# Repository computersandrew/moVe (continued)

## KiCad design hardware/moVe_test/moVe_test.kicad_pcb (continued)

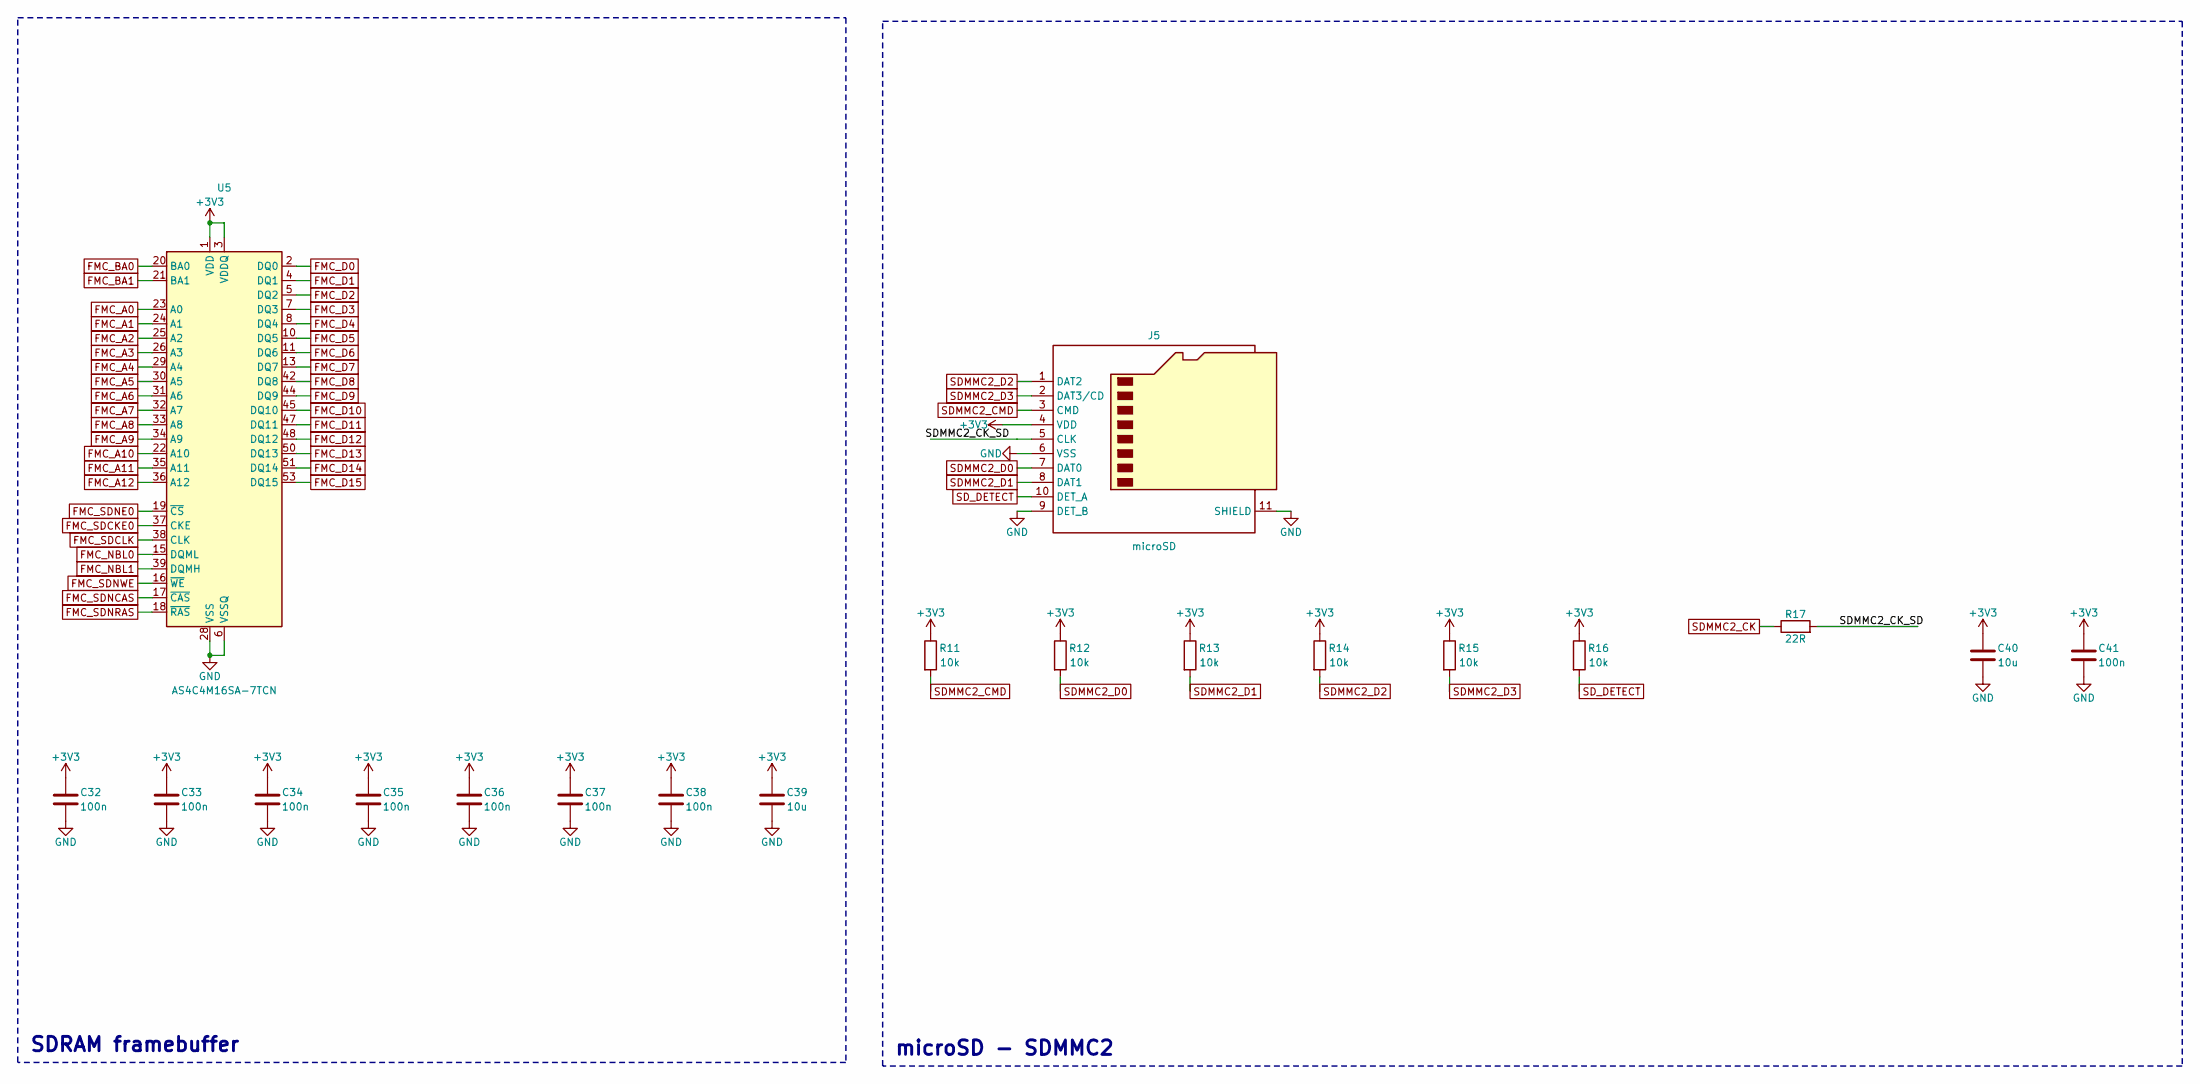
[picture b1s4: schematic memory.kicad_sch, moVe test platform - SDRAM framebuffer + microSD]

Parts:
C32, C33, C34, C35, C36, C37, C38, C41: 100n; C_0603_1608Metric
C39, C40: 10u; C_0805_2012Metric
J5: microSD; microSD_HC_Molex_104031-0811; MPN 1040310811
R11, R12, R13, R14, R15, R16: 10k; R_0603_1608Metric
R17: 22R; R_0603_1608Metric
U5: AS4C4M16SA-7TCN; TSOP-II-54_22.2x10.16mm_P0.8mm; MPN AS4C4M16SA-7TCN (alt MT48LC16M16A2P-6A: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

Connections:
+3V3: C32.1, C33.1, C34.1, C35.1, C36.1, C37.1, C38.1, C39.1, C40.1, C41.1, J5.4 (VDD), R11.1, R12.1, R13.1, R14.1, R15.1, R16.1, U5.1 (VDD), U5.3 (VDDQ), U5.9 (VDDQ), U5.14 (VDD), U5.27 (VDD), U5.43 (VDDQ), U5.49 (VDDQ); also elsewhere on the board
/Memory/SDMMC2_CK_SD: J5.5 (CLK), R17.2
FMC_A0: U5.23 (A0); also elsewhere on the board
FMC_A1: U5.24 (A1); also elsewhere on the board
FMC_A2: U5.25 (A2); also elsewhere on the board
FMC_A3: U5.26 (A3); also elsewhere on the board
FMC_A4: U5.29 (A4); also elsewhere on the board
FMC_A5: U5.30 (A5); also elsewhere on the board
FMC_A6: U5.31 (A6); also elsewhere on the board
FMC_A7: U5.32 (A7); also elsewhere on the board
FMC_A8: U5.33 (A8); also elsewhere on the board
FMC_A9: U5.34 (A9); also elsewhere on the board
FMC_A10: U5.22 (A10); also elsewhere on the board
FMC_A11: U5.35 (A11); also elsewhere on the board
FMC_A12: U5.36 (A12); also elsewhere on the board
FMC_BA0: U5.20 (BA0); also elsewhere on the board
FMC_BA1: U5.21 (BA1); also elsewhere on the board
FMC_D0: U5.2 (DQ0); also elsewhere on the board
FMC_D1: U5.4 (DQ1); also elsewhere on the board
FMC_D2: U5.5 (DQ2); also elsewhere on the board
FMC_D3: U5.7 (DQ3); also elsewhere on the board
FMC_D4: U5.8 (DQ4); also elsewhere on the board
FMC_D5: U5.10 (DQ5); also elsewhere on the board
FMC_D6: U5.11 (DQ6); also elsewhere on the board
FMC_D7: U5.13 (DQ7); also elsewhere on the board
FMC_D8: U5.42 (DQ8); also elsewhere on the board
FMC_D9: U5.44 (DQ9); also elsewhere on the board
FMC_D10: U5.45 (DQ10); also elsewhere on the board
FMC_D11: U5.47 (DQ11); also elsewhere on the board
FMC_D12: U5.48 (DQ12); also elsewhere on the board
FMC_D13: U5.50 (DQ13); also elsewhere on the board
FMC_D14: U5.51 (DQ14); also elsewhere on the board
FMC_D15: U5.53 (DQ15); also elsewhere on the board
FMC_NBL0: U5.15 (DQML); also elsewhere on the board
FMC_NBL1: U5.39 (DQMH); also elsewhere on the board
FMC_SDCKE0: U5.37 (CKE); also elsewhere on the board
FMC_SDCLK: U5.38 (CLK); also elsewhere on the board
FMC_SDNCAS: U5.17 (~CAS); also elsewhere on the board
FMC_SDNE0: U5.19 (~CS); also elsewhere on the board
FMC_SDNRAS: U5.18 (~RAS); also elsewhere on the board
FMC_SDNWE: U5.16 (~WE); also elsewhere on the board
GND: C32.2, C33.2, C34.2, C35.2, C36.2, C37.2, C38.2, C39.2, C40.2, C41.2, J5.6 (VSS), J5.9 (DET_B), J5.11 (SHIELD), U5.6 (VSSQ), U5.12 (VSSQ), U5.28 (VSS), U5.41 (VSS), U5.46 (VSSQ), U5.52 (VSSQ), U5.54 (VSS); also elsewhere on the board
SDMMC2_CK: R17.1; also elsewhere on the board
SDMMC2_CMD: J5.3 (CMD), R11.2; also elsewhere on the board
SDMMC2_D0: J5.7 (DAT0), R12.2; also elsewhere on the board
SDMMC2_D1: J5.8 (DAT1), R13.2; also elsewhere on the board
SDMMC2_D2: J5.1 (DAT2), R14.2; also elsewhere on the board
SDMMC2_D3: J5.2 (DAT3/CD), R15.2; also elsewhere on the board
SD_DETECT: J5.10 (DET_A), R16.2; also elsewhere on the board

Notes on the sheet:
SDRAM framebuffer
microSD - SDMMC2

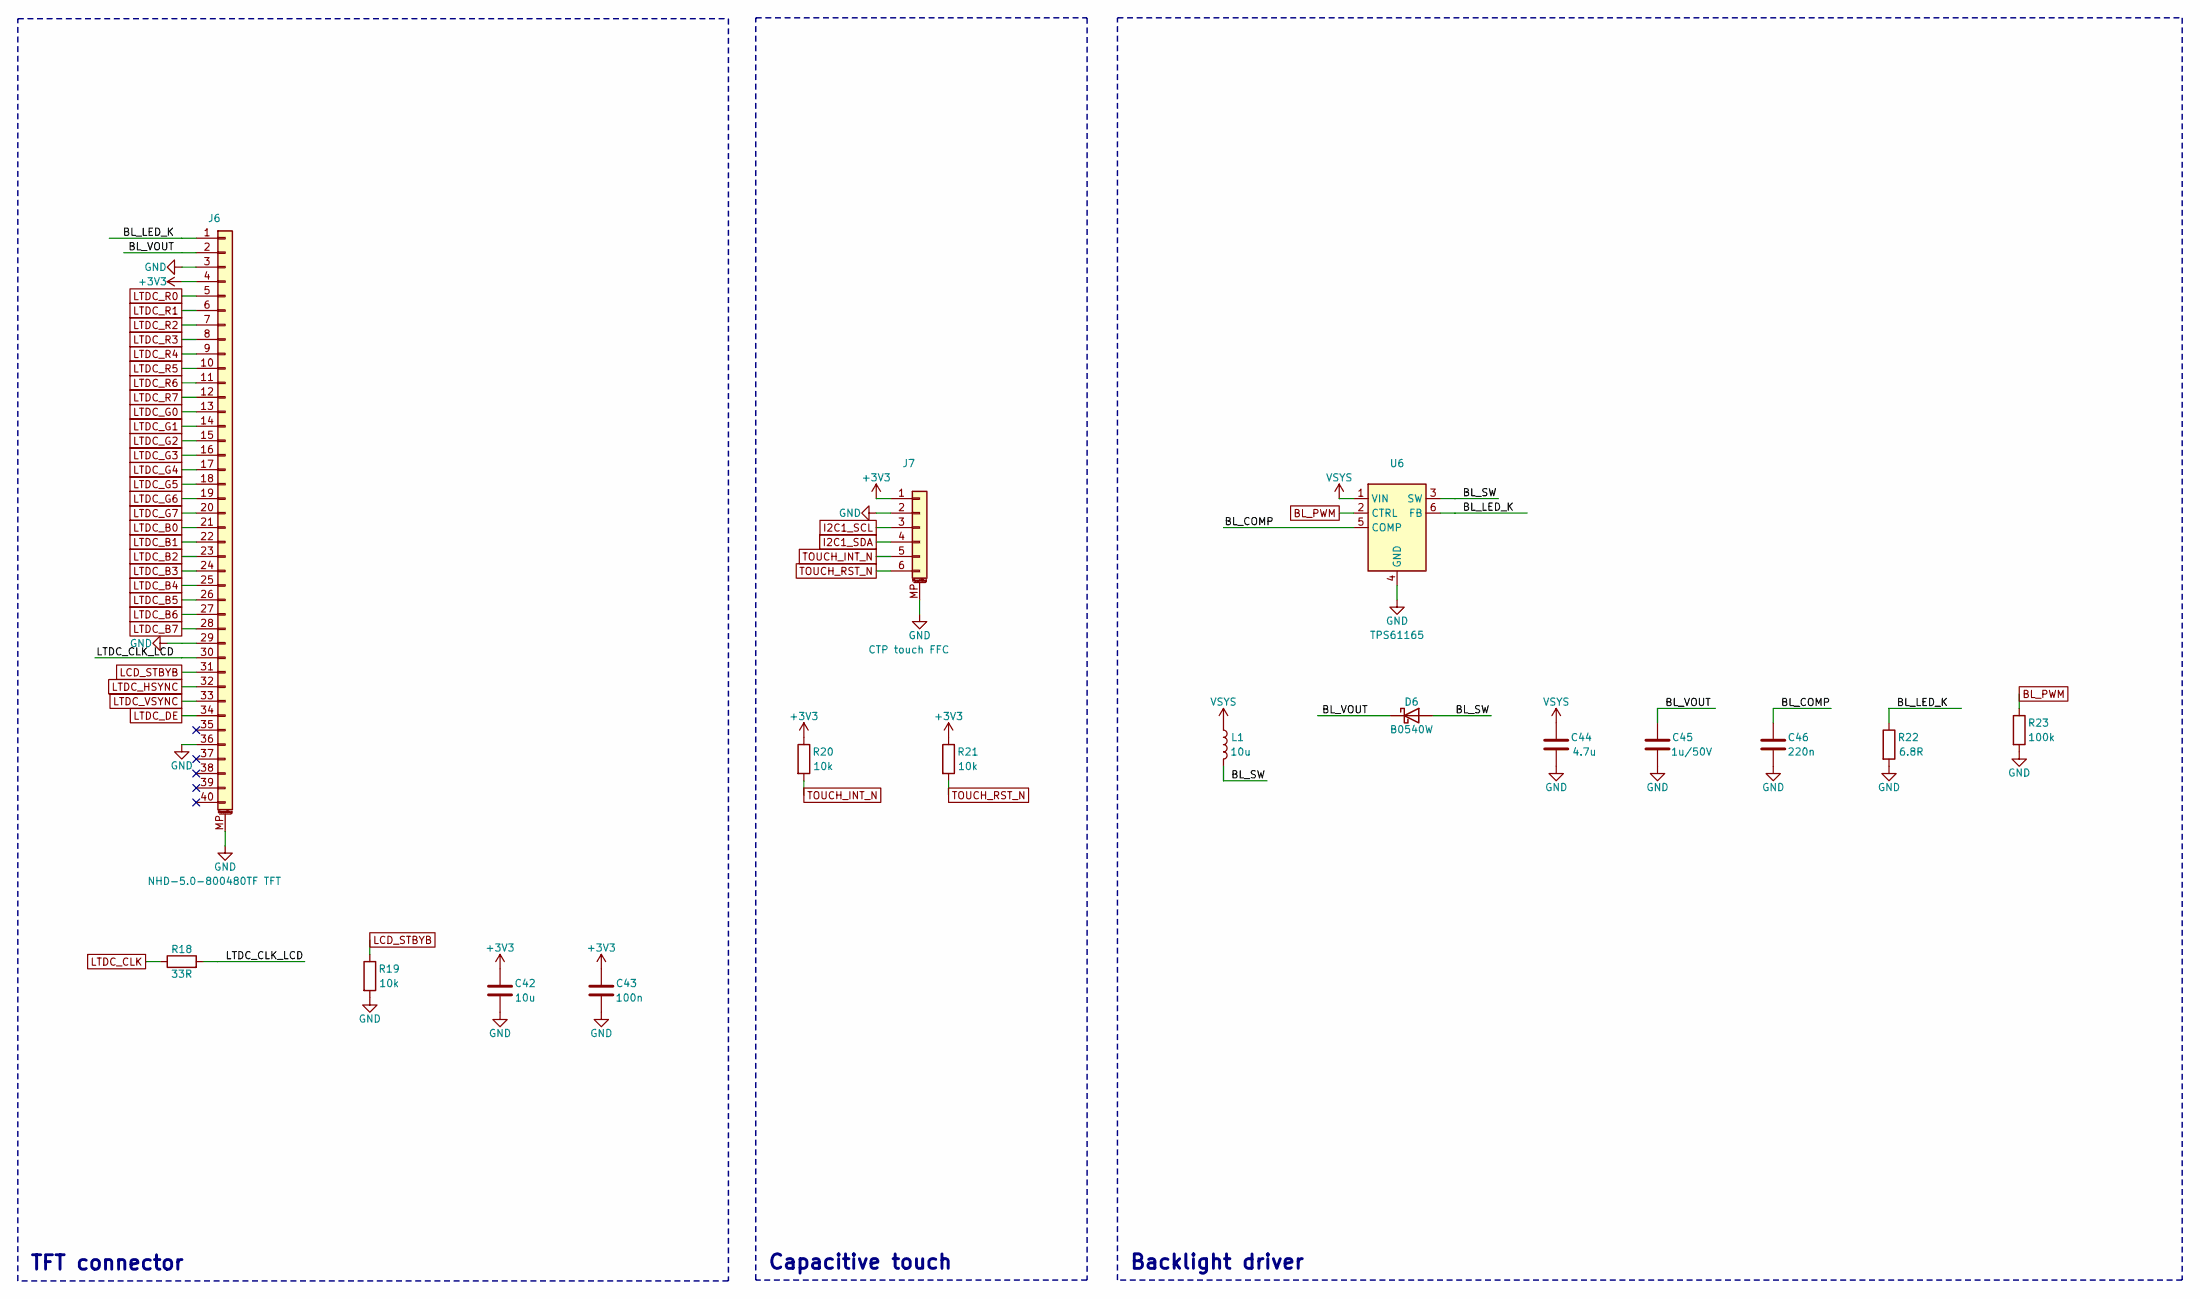
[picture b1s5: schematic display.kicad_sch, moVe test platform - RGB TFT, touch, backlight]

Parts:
C42: 10u; C_0805_2012Metric
C43: 100n; C_0603_1608Metric
C44: 4.7u; C_0805_2012Metric
C45: 1u/50V; C_0805_2012Metric
C46: 220n; C_0603_1608Metric
D6: B0540W; D_SOD-123; MPN B0540W-7-F
J6: NHD-5.0-800480TF TFT; Hirose_FH12-40S-0.5SH_1x40-1MP_P0.50mm_Horizontal; MPN FH12-40S-0.5SH(55) (display spec lists 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
J7: CTP touch FFC; Molex_200528-0060_1x06-1MP_P1.00mm_Horizontal; MPN Molex 200528-0060 (display spec lists 5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
L1: 10u; L_Bourns-SRN4018; MPN SRN4018-100M
R18: 33R; R_0603_1608Metric
R19, R20, R21: 10k; R_0603_1608Metric
R22: 6.8R; R_0603_1608Metric
R23: 100k; R_0603_1608Metric
U6: TPS61165; SOT-23-6; MPN TPS61165DBVR

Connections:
+3V3: C42.1, C43.1, J6.4, J7.1, R20.1, R21.1; also elsewhere on the board
/Display/BL_COMP: C46.1, U6.5 (COMP)
/Display/BL_LED_K: J6.1, R22.1, U6.6 (FB)
/Display/BL_SW: D6.2 (A), L1.2, U6.3 (SW)
/Display/BL_VOUT: C45.1, D6.1 (K), J6.2
/Display/LTDC_CLK_LCD: J6.30, R18.2
BL_PWM: R23.1, U6.2 (CTRL); also elsewhere on the board
GND: C42.2, C43.2, C44.2, C45.2, C46.2, J6.3, J6.29, J6.36, J6.MP (MountPin), J7.2, J7.MP (MountPin), R19.2, R22.2, R23.2, U6.4 (GND); also elsewhere on the board
I2C1_SCL: J7.3; also elsewhere on the board
I2C1_SDA: J7.4; also elsewhere on the board
LCD_STBYB: J6.31, R19.1; also elsewhere on the board
LTDC_B0: J6.21; also elsewhere on the board
LTDC_B1: J6.22; also elsewhere on the board
LTDC_B2: J6.23; also elsewhere on the board
LTDC_B3: J6.24; also elsewhere on the board
LTDC_B4: J6.25; also elsewhere on the board
LTDC_B5: J6.26; also elsewhere on the board
LTDC_B6: J6.27; also elsewhere on the board
LTDC_B7: J6.28; also elsewhere on the board
LTDC_CLK: R18.1; also elsewhere on the board
LTDC_DE: J6.34; also elsewhere on the board
LTDC_G0: J6.13; also elsewhere on the board
LTDC_G1: J6.14; also elsewhere on the board
LTDC_G2: J6.15; also elsewhere on the board
LTDC_G3: J6.16; also elsewhere on the board
LTDC_G4: J6.17; also elsewhere on the board
LTDC_G5: J6.18; also elsewhere on the board
LTDC_G6: J6.19; also elsewhere on the board
LTDC_G7: J6.20; also elsewhere on the board
LTDC_HSYNC: J6.32; also elsewhere on the board
LTDC_R0: J6.5; also elsewhere on the board
LTDC_R1: J6.6; also elsewhere on the board
LTDC_R2: J6.7; also elsewhere on the board
LTDC_R3: J6.8; also elsewhere on the board
LTDC_R4: J6.9; also elsewhere on the board
LTDC_R5: J6.10; also elsewhere on the board
LTDC_R6: J6.11; also elsewhere on the board
LTDC_R7: J6.12; also elsewhere on the board
LTDC_VSYNC: J6.33; also elsewhere on the board
TOUCH_INT_N: J7.5, R20.2; also elsewhere on the board
TOUCH_RST_N: J7.6, R21.2; also elsewhere on the board
VSYS: C44.1, L1.1, U6.1 (VIN); also elsewhere on the board

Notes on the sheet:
TFT connector
Capacitive touch
Backlight driver

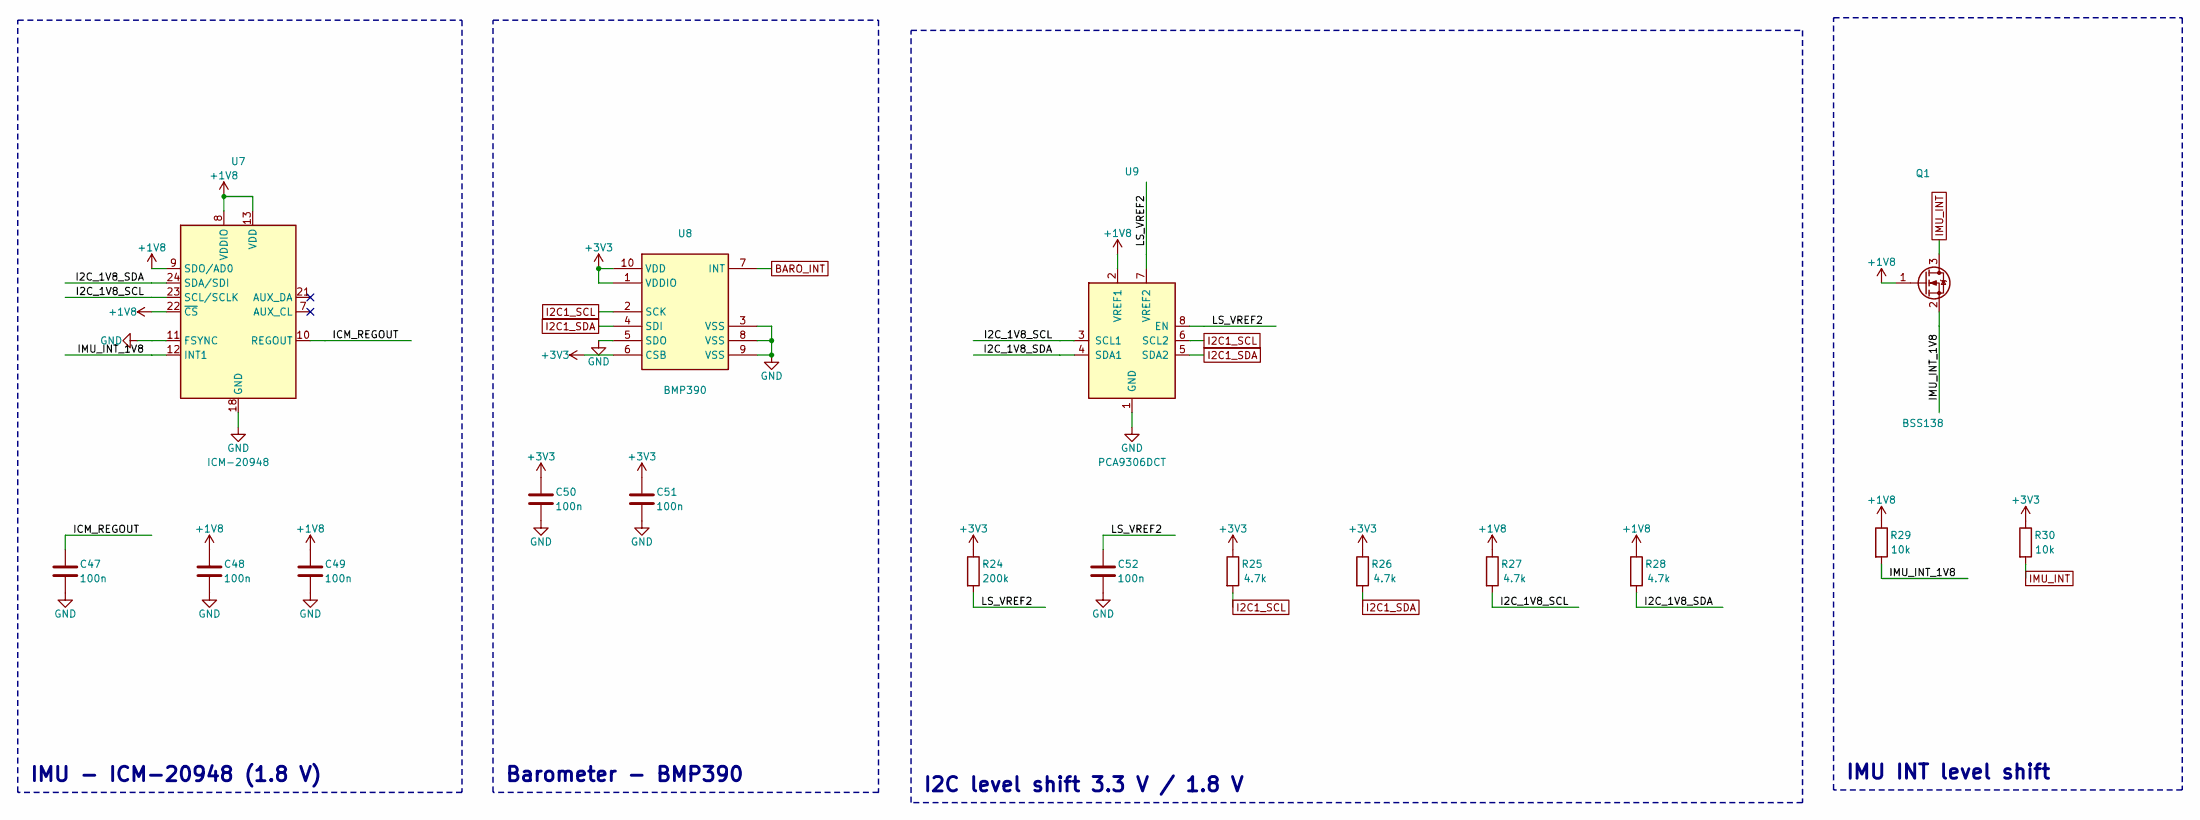
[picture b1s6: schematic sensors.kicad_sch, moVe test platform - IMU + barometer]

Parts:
C47, C48, C49, C50, C51, C52: 100n; C_0603_1608Metric
Q1: BSS138; SOT-23; MPN BSS138
R24: 200k; R_0603_1608Metric
R25, R26, R27, R28: 4.7k; R_0603_1608Metric
R29, R30: 10k; R_0603_1608Metric
U7: ICM-20948; InvenSense_QFN-24_3x3mm_P0.4mm; MPN ICM-20948
U8: BMP390; Bosch_LGA-10_2x2mm_P0.5mm; MPN BMP390
U9: PCA9306DCT; SSOP-8_2.95x2.8mm_P0.65mm; MPN PCA9306DCTR

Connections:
+1V8: C48.1, C49.1, Q1.1 (G), R27.1, R28.1, R29.1, U7.8 (VDDIO), U7.9 (SDO/AD0), U7.13 (VDD), U7.22 (~CS), U9.2 (VREF1); also elsewhere on the board
+3V3: C50.1, C51.1, R24.1, R25.1, R26.1, R30.1, U8.1 (VDDIO), U8.6 (CSB), U8.10 (VDD); also elsewhere on the board
/Sensors/I2C_1V8_SCL: R27.2, U7.23 (SCL/SCLK), U9.3 (SCL1)
/Sensors/I2C_1V8_SDA: R28.2, U7.24 (SDA/SDI), U9.4 (SDA1)
/Sensors/ICM_REGOUT: C47.1, U7.10 (REGOUT)
/Sensors/IMU_INT_1V8: Q1.2 (S), R29.2, U7.12 (INT1)
/Sensors/LS_VREF2: C52.1, R24.2, U9.7 (VREF2), U9.8 (EN)
BARO_INT: U8.7 (INT); also elsewhere on the board
GND: C47.2, C48.2, C49.2, C50.2, C51.2, C52.2, U7.11 (FSYNC), U7.18 (GND), U7.20 (GND), U8.3 (VSS), U8.5 (SDO), U8.8 (VSS), U8.9 (VSS), U9.1 (GND); also elsewhere on the board
I2C1_SCL: R25.2, U8.2 (SCK), U9.6 (SCL2); also elsewhere on the board
I2C1_SDA: R26.2, U8.4 (SDI), U9.5 (SDA2); also elsewhere on the board
IMU_INT: Q1.3 (D), R30.2; also elsewhere on the board

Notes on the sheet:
IMU - ICM-20948 (1.8 V)
Barometer - BMP390
I2C level shift 3.3 V / 1.8 V
IMU INT level shift

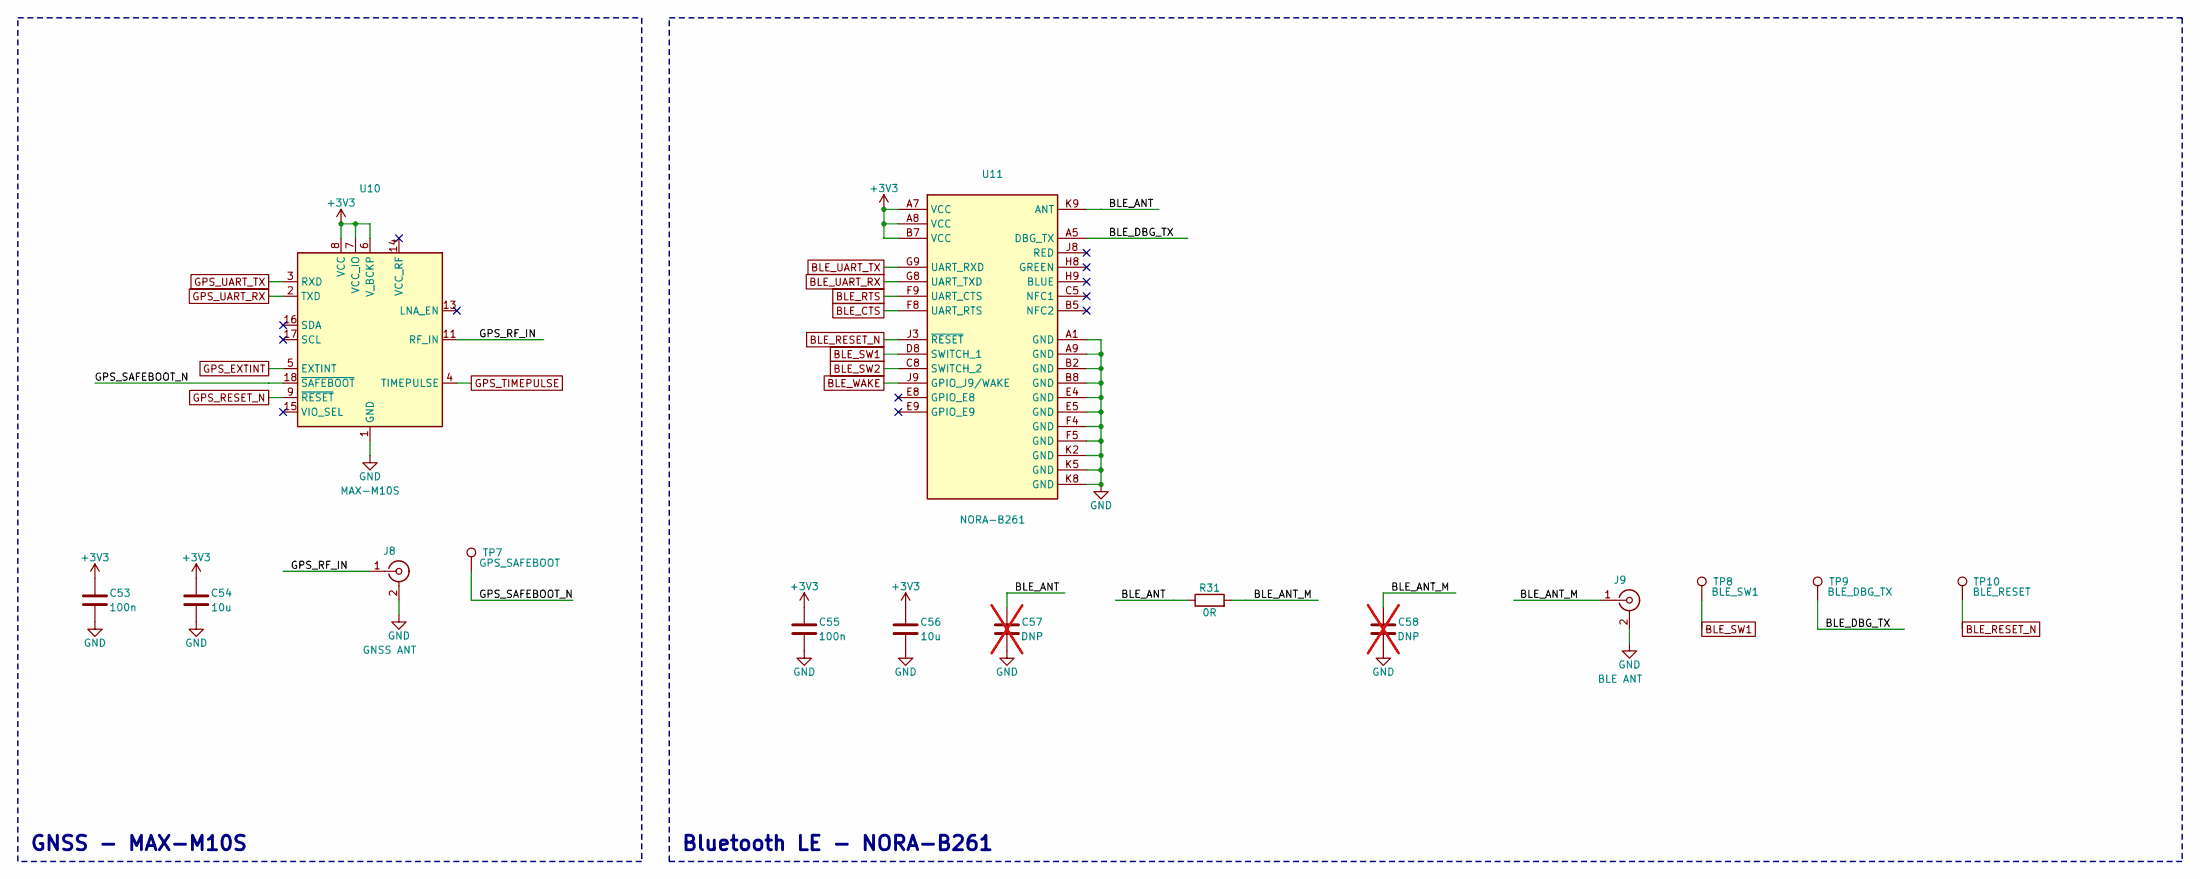
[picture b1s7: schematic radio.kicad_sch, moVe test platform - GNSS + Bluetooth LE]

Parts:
C53, C55: 100n; C_0603_1608Metric
C54, C56: 10u; C_0805_2012Metric
C57, C58: DNP; C_0402_1005Metric; not fitted
J8: GNSS ANT; U.FL_Hirose_U.FL-R-SMT-1_Vertical; MPN U.FL-R-SMT-1(10)
J9: BLE ANT; U.FL_Hirose_U.FL-R-SMT-1_Vertical; MPN U.FL-R-SMT-1(10)
R31: 0R; R_0402_1005Metric
TP7: GPS_SAFEBOOT; TestPoint_Pad_D1.5mm
TP8: BLE_SW1; TestPoint_Pad_D1.5mm
TP9: BLE_DBG_TX; TestPoint_Pad_D1.5mm
TP10: BLE_RESET; TestPoint_Pad_D1.5mm
U10: MAX-M10S; ublox_MAX; MPN MAX-M10S-00B
U11: NORA-B261; ublox_NORA-B2x1; MPN NORA-B261-00B

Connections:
+3V3: C53.1, C54.1, C55.1, C56.1, U10.6 (V_BCKP), U10.7 (VCC_IO), U10.8 (VCC), U11.A7 (VCC), U11.A8 (VCC), U11.B7 (VCC); also elsewhere on the board
/Radio/BLE_ANT: C57.1, R31.1, U11.K9 (ANT)
/Radio/BLE_ANT_M: C58.1, J9.1 (In), R31.2
/Radio/BLE_DBG_TX: TP9.1, U11.A5 (DBG_TX)
/Radio/GPS_RF_IN: J8.1 (In), U10.11 (RF_IN)
/Radio/GPS_SAFEBOOT_N: TP7.1, U10.18 (~SAFEBOOT)
BLE_CTS: U11.F8 (UART_RTS); also elsewhere on the board
BLE_RESET_N: TP10.1, U11.J3 (~RESET); also elsewhere on the board
BLE_RTS: U11.F9 (UART_CTS); also elsewhere on the board
BLE_SW1: TP8.1, U11.D8 (SWITCH_1); also elsewhere on the board
BLE_SW2: U11.C8 (SWITCH_2); also elsewhere on the board
BLE_UART_RX: U11.G8 (UART_TXD); also elsewhere on the board
BLE_UART_TX: U11.G9 (UART_RXD); also elsewhere on the board
BLE_WAKE: U11.J9 (GPIO_J9/WAKE); also elsewhere on the board
GND: C53.2, C54.2, C55.2, C56.2, C57.2, C58.2, J8.2 (Ext), J9.2 (Ext), U10.1 (GND), U10.10 (GND), U10.12 (GND), U11.A1 (GND), U11.A9 (GND), U11.B2 (GND), U11.B8 (GND), U11.E4 (GND), U11.E5 (GND), U11.F4 (GND), U11.F5 (GND), U11.K2 (GND), U11.K5 (GND), U11.K8 (GND); also elsewhere on the board
GPS_EXTINT: U10.5 (EXTINT); also elsewhere on the board
GPS_RESET_N: U10.9 (~RESET); also elsewhere on the board
GPS_TIMEPULSE: U10.4 (TIMEPULSE); also elsewhere on the board
GPS_UART_RX: U10.2 (TXD); also elsewhere on the board
GPS_UART_TX: U10.3 (RXD); also elsewhere on the board

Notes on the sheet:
GNSS - MAX-M10S
Bluetooth LE - NORA-B261

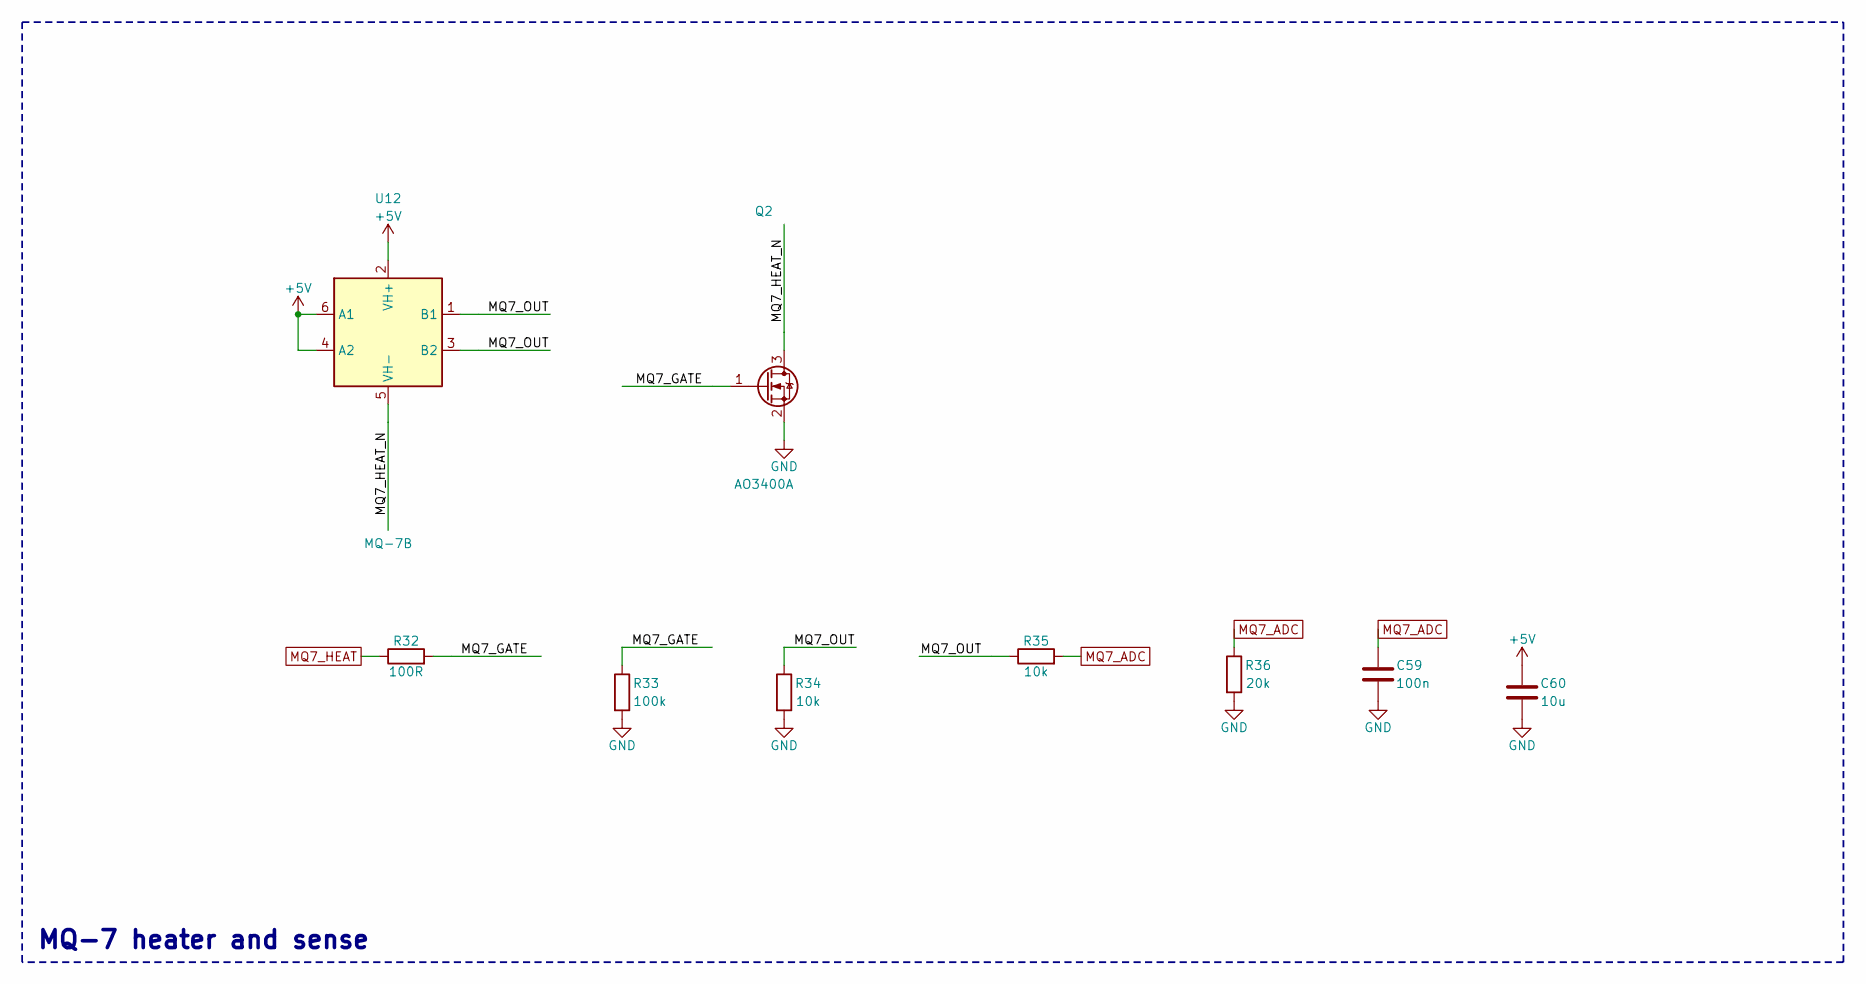
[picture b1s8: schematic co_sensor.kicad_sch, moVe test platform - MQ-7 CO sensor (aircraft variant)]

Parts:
C59: 100n; C_0603_1608Metric
C60: 10u; C_0805_2012Metric
Q2: AO3400A; SOT-23; MPN AO3400A
R32: 100R; R_0603_1608Metric
R33: 100k; R_0603_1608Metric
R34, R35: 10k; R_0603_1608Metric
R36: 20k; R_0603_1608Metric
U12: MQ-7B; MQ-6; MPN Winsen MQ-7B (aircraft build only)

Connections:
+5V: C60.1, U12.2 (VH+), U12.4 (A2), U12.6 (A1); also elsewhere on the board
/CO_Sensor/MQ7_GATE: Q2.1 (G), R32.2, R33.1
/CO_Sensor/MQ7_HEAT_N: Q2.3 (D), U12.5 (VH-)
/CO_Sensor/MQ7_OUT: R34.1, R35.1, U12.1 (B1), U12.3 (B2)
GND: C59.2, C60.2, Q2.2 (S), R33.2, R34.2, R36.2; also elsewhere on the board
MQ7_ADC: C59.1, R35.2, R36.1; also elsewhere on the board
MQ7_HEAT: R32.1; also elsewhere on the board

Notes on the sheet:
MQ-7 heater and sense
